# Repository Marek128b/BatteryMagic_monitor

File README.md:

# BatteryMagic_monitor

**Table of Contents**
- [BatteryMagic\_monitor](#batterymagic_monitor)
  - [description](#description)

## description

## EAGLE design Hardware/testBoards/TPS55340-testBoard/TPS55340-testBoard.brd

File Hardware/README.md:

# Hardware

**Table of Contents**
- [Hardware](#hardware)
  - [description](#description)
  - [Schematic](#schematic)
    - [Link](#link)
  - [PCB](#pcb)
  - [diagramm](#diagramm)
  - [Iset](#iset)
    - [calculations](#calculations)
    - [Multisim circuit](#multisim-circuit)

---
## description

<br>

---
## Schematic
### Link
https://easyeda.com/editor#id=32b7ace7bde44caea4c9ae37066067a1|f48f90d7611346188e835fb0149f18e7

## PCB

---
## diagramm

---
## Iset

### calculations

Therefore V_ISET = 0,200V to 2,0V when R_SR = 10m Ohm and I_CHARGE from 1A to 10A. <br>

### Multisim circuit

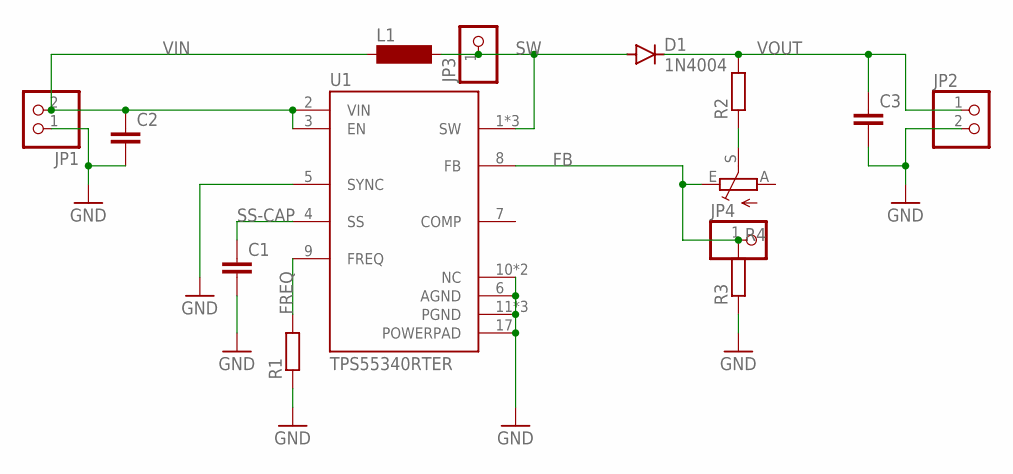
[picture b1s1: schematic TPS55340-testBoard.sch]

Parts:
C1, C2, C3: C5/5; C5B5
D1: 1N4004; DO41-10
JP1, JP2: PINHD-1X2/90; 1X02/90
JP3, JP4: PINHD-1X1; 1X01
L1: BS75
R1, R2, R3: R-EU_VMTB60; VMTB60
R4: TRIM_EU-CA9V; CA9V
U1: TPS55340RTER; QFN50P300X300X80-17N

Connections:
FB: JP4.1, R3.2, R4.E, U1.8 (FB)
FREQ: R1.2, U1.9 (FREQ)
GND: C1.2, C2.2, C3.2, JP1.1, JP2.2, R1.1, R3.1, U1.5 (SYNC), U1.6 (AGND), U1.10 (NC), U1.11 (PGND), U1.12 (PGND), U1.13 (PGND), U1.14 (NC), U1.17 (POWERPAD)
unnamed: R2.1, R4.S
SS-CAP: C1.1, U1.4 (SS)
SW: D1.A, JP3.1, L1.2, U1.1 (SW), U1.15 (SW), U1.16 (SW)
VIN: C2.1, JP1.2, L1.1, U1.2 (VIN), U1.3 (EN)
VOUT: C3.1, D1.C, JP2.1, R2.2

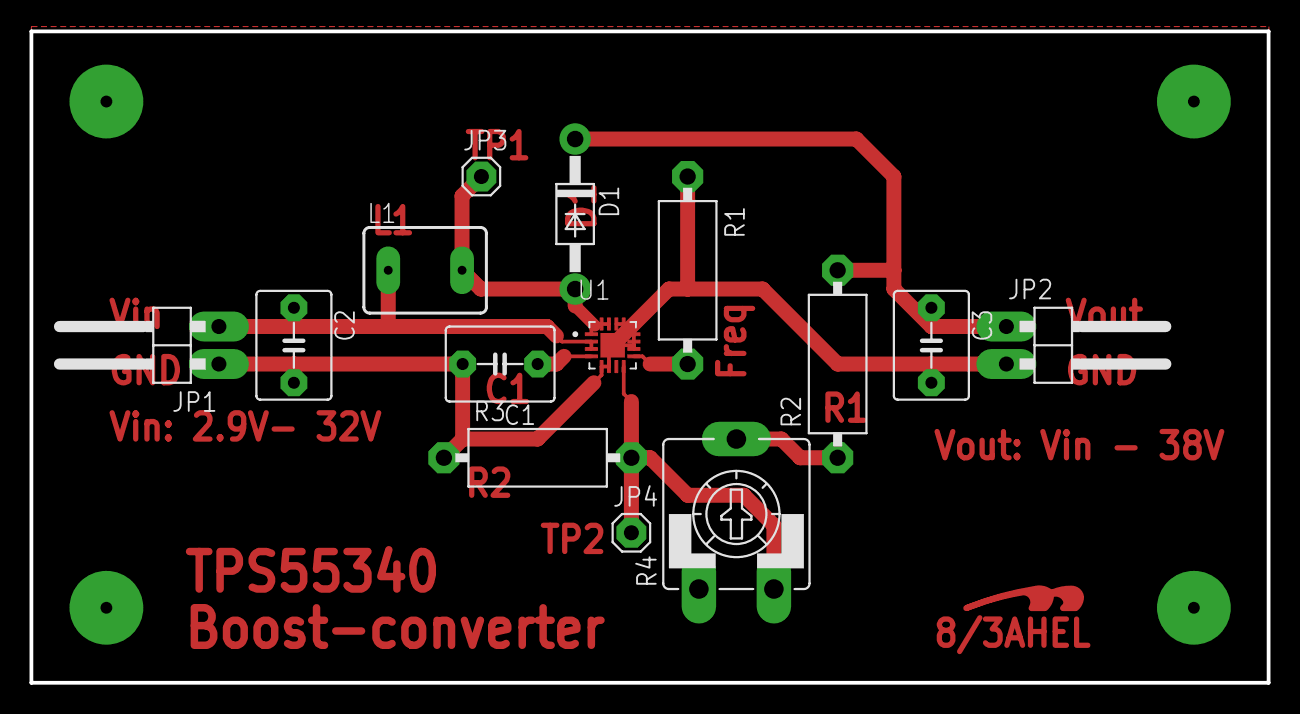
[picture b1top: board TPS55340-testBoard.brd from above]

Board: 2 copper layers, 83.8 x 44.1 mm, 15 parts (0 on the bottom side), 8 nets.

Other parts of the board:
U$1: LOGOTOP_8

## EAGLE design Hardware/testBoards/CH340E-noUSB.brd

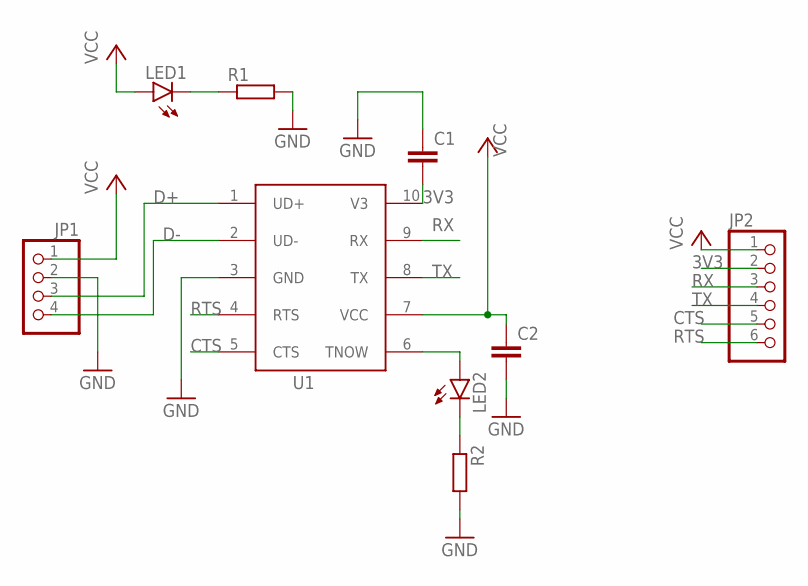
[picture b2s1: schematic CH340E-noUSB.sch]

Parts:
C1, C2: C-EUC0603; C0603
JP1: PINHD-1X4; 1X04
JP2: PINHD-1X6/90; 1X06/90
LED1, LED2: LEDCHIP-LED0603; CHIP-LED0603
R1, R2: R-EU_R0603; R0603
U1: CH340ESMD; MSOP10

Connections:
3V3: C1.2, JP2.2, U1.10 (V3)
CTS: JP2.5, U1.5 (CTS)
D+: JP1.3, U1.1 (UD+)
D-: JP1.4, U1.2 (UD-)
GND: C1.1, C2.2, JP1.2, R1.2, R2.2, U1.3 (GND)
unnamed: LED1.C, R1.1
unnamed: LED2.A, U1.6 (TNOW)
unnamed: LED2.C, R2.1
RTS: JP2.6, U1.4 (RTS)
RX: JP2.3, U1.9 (RX)
TX: JP2.4, U1.8 (TX)
VCC: C2.1, JP1.1, JP2.1, LED1.A, U1.7 (VCC)

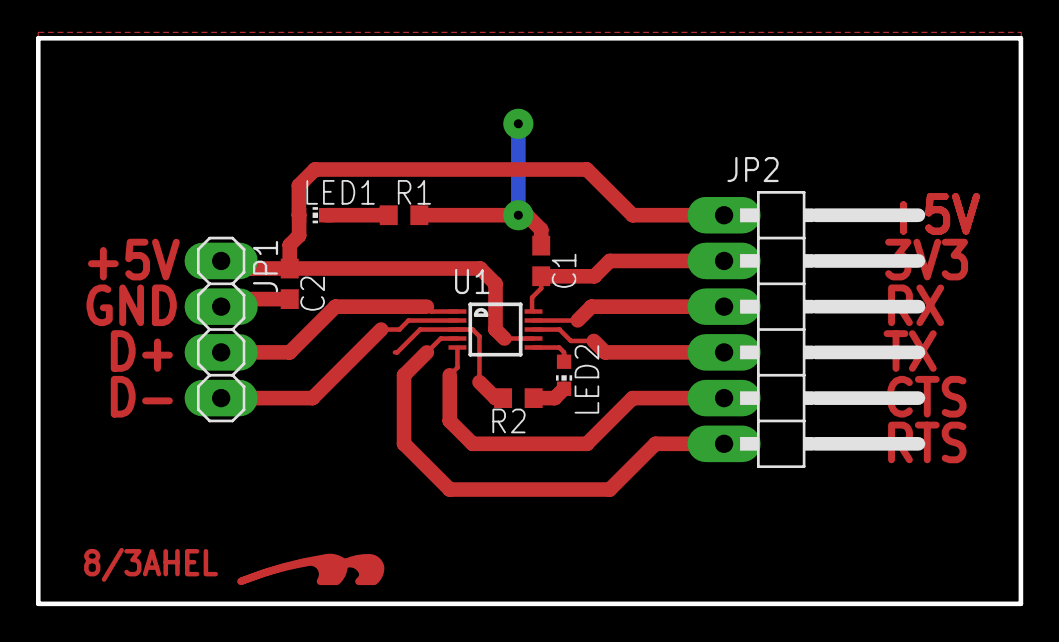
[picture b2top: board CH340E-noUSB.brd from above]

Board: 2 copper layers, 54.6 x 31.4 mm, 10 parts (0 on the bottom side), 12 nets.

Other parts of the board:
U$1: LOGOTOP_8

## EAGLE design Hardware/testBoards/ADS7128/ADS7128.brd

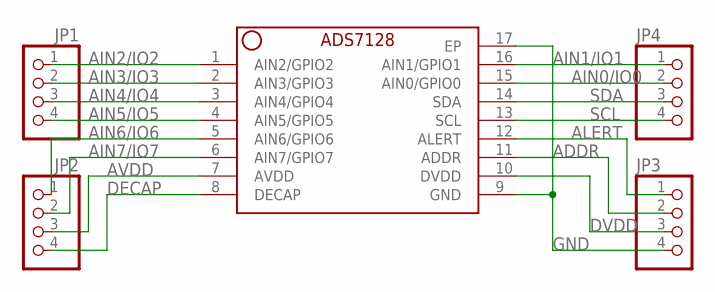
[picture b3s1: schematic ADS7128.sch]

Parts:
JP1, JP2, JP3, JP4: PINHD-1X4; 1X04
U$1: ADS7128; QFN50P300X300X80-17N

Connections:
ADDR: JP3.2, U$1.11 (ADDR)
AIN0/IO0: JP4.2, U$1.15 (AIN0/GPIO0)
AIN1/IO1: JP4.1, U$1.16 (AIN1/GPIO1)
AIN2/IO2: JP1.1, U$1.1 (AIN2/GPIO2)
AIN3/IO3: JP1.2, U$1.2 (AIN3/GPIO3)
AIN4/IO4: JP1.3, U$1.3 (AIN4/GPIO4)
AIN5/IO5: JP1.4, U$1.4 (AIN5/GPIO5)
AIN6/IO6: JP2.1, U$1.5 (AIN6/GPIO6)
AIN7/IO7: JP2.2, U$1.6 (AIN7/GPIO7)
ALERT: JP3.1, U$1.12 (ALERT)
AVDD: JP2.3, U$1.7 (AVDD)
DECAP: JP2.4, U$1.8 (DECAP)
DVDD: JP3.3, U$1.10 (DVDD)
GND: JP3.4, U$1.9 (GND), U$1.17 (EP)
SCL: JP4.4, U$1.13 (SCL)
SDA: JP4.3, U$1.14 (SDA)

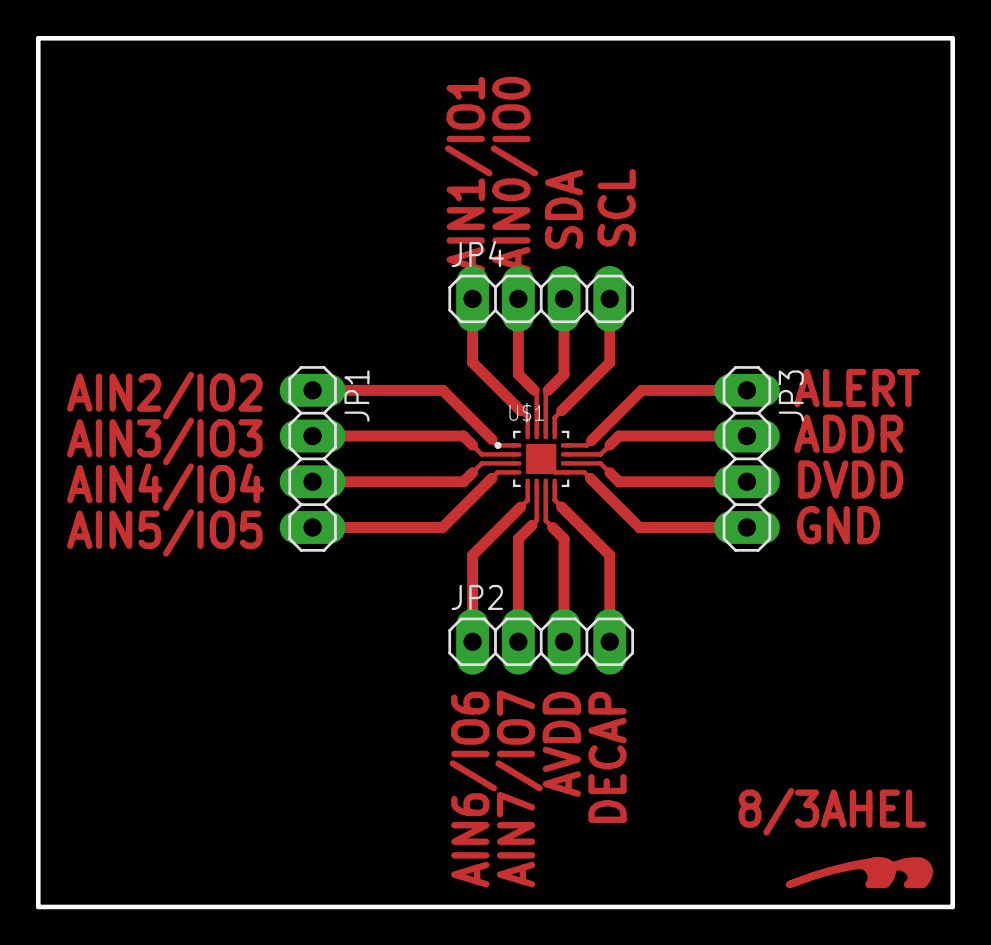
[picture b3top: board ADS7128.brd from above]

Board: 2 copper layers, 50.8 x 48.3 mm, 6 parts (0 on the bottom side), 16 nets.

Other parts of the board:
U$2: LOGOTOP_8

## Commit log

2023-04-17 added basic readme
2023-04-17 added first drawio diagramm
2023-04-17 added drawing and pictures
2023-04-17 added basic description of hardware basic
2023-04-18 Added Diagramm
2023-04-27 AkkuMagic.drawio aktualisiert
2023-04-27 AkkuMagic.drawio aktualisiert2
2023-04-27 AkkuMagic.drawio.svg eingefügt
2023-04-27 added schematic and pcb
2023-04-27 added schematics and pcb to Readme
2023-04-27 chanched width pcb image in readme
2023-05-02 added uC basic program
2023-05-02 added wifiManager test
2023-05-02 added Wifi AP code V1
2023-05-02 added WiFi better AP 1
2023-05-02 added WiFi configuration file using SPIFFS FS
2023-05-02 added function reset AP on Reboot reset after web
2023-05-03 added html focus
2023-05-03 added test login page with better design
2023-05-03 added test html block
2023-05-03 added firebase code erroer: 100.6% of storage
2023-05-04 added partition test code
2023-05-04 added firebase project
2023-05-04 changed code to work with more flash(partition)
2023-05-06 added LogIn and SignIn Web Page
2023-05-06 added style.css files for main Page and signIn
2023-05-06 changed main Page design
2023-05-06 added npm inst. fb. + first test read rtdb worked
2023-05-06 added sign In form
2023-05-07 added login signin form html css js responsive
2023-05-07 added js for auth
2023-05-07 added nodeJS chart.js
2023-05-07 added basic Dashboard
2023-05-07 added working chart using v2.7.3
2023-05-07 added test.json for the db
2023-05-07 changed to newest version of Chart.js
2023-05-07 changed test.json data to be better to work with
2023-05-07 added dashboard style
2023-05-07 added headder for web page signin up
2023-05-07 added dashboard styles
2023-05-07 added contact page and links
2023-05-07 added dark-mode script
2023-05-07 added dark-mode-logic
2023-05-07 better dark-mode
2023-05-07 added dxf + bmp of cardboard and paper prototypes
2023-05-07 fixed error
2023-05-07 added signIn and signUp js
2023-05-08 fixed login screen and added user feedback
2023-05-08 added global variables
2023-05-08 added rtdb to dashboard
2023-05-08 added is Signed in val
2023-05-08 fixed merge conflict main.cpp
2023-05-08 added NoDelay library
2023-05-08 removed NoDelay due to error
2023-05-08 added first working database write esp32
2023-05-08 added firebase json data working
2023-05-09 fixed debug message switch
2023-06-01 added test Boards for the magic Monitor
2023-06-01 added blockschaltbild v1
2023-06-01 added programming header with uart
2023-06-01 added schaltbild1
2023-06-23 added korzbeschreibung V1
2023-10-17 added test boards from easysda
2023-10-24 added new schematic and pcb pictures test boost #4
2023-12-19 added low pass filter ms simulation and pictures for charge current set
2024-01-19 added bq24600 tests; test Battery charger IC #12
